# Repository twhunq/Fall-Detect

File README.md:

# Hệ thống IoT Phát hiện & Cảnh báo Té ngã (`Fall_detect`)

Hệ thống giám sát và cảnh báo té ngã đa tầng cho người cao tuổi, kết hợp hai nhánh phần cứng AI tại biên (**Edge AI**) và nền tảng **Cloud Realtime**:

1. **Thiết bị đeo TinyML (`firmware/wearable/`)**: Vi điều khiển **ESP32-S3 Super Mini** + cảm biến quán tính 6 trục **MPU6050**, chạy mô hình mạng nơ-ron **MLP (30 → 16 → 8 → 5)** kết hợp xác nhận động học sau va đập, cảnh báo còi/LED tại chỗ, cấu hình qua Web Portal nội bộ, đồng bộ **Firebase Realtime Database** và gửi tin khẩn cấp qua **Telegram / Gmail**.
2. **Thiết bị Camera AI (`firmware/camera-k230/`)**: Camera **CanMV K230** chạy mô hình thị giác **YOLOv5n** + bộ theo dõi đa đối tượng IoU + bỏ phiếu M-trong-N, kết nối UART tốc độ cao (`921600 baud`) sang **ESP32-S3 DevKitC-1 N16R8** để phát cảnh báo **BLE 5.0** (xác thực `HMAC-SHA256`), đẩy ảnh bằng chứng lên Relay và phát luồng video trực tiếp **MJPEG**.
3. **Cloud & Web Dashboard (`cloud/`)**: Trang giám sát thời gian thực và phân quyền người dùng trên **Firebase Hosting & Realtime Database**.
4. **Ứng dụng di động "Báo Ngã IoT" (`mobile/`)**: Flutter đa nền tảng (Android `.apk`, iOS `.ipa` chưa ký cài bằng **Sideloadly**), nghe song song 4 đường cảnh báo (UDP LAN, BLE camera, Firebase SSE, Web Portal nội mạng), hú còi/rung/màn hình báo động đỏ khi đường nhanh nhất tới, khử trùng lặp và hợp nhất "Vòng đeo + Camera AI" trong 30 giây.
5. **Phần cứng PCB (`hardware/pcb/`)**: Thiết kế mạch nguyên lý, PCB 2 lớp `60 × 50 mm` (KiCad 10), mô hình 3D `.step`, BOM và file Gerber sẵn sàng gia công.

---

## Cấu trúc thư mục dự án

```text
Fall_detect/
├── firmware/
│   ├── wearable/                  # Thiết bị đeo ESP32-S3 Super Mini + TinyML
│   │   ├── src/
│   │   │   ├── fall_detection_esp32/  # Firmware chính (C++17, header-only)
│   │   │   └── data_collection/       # Sketch thu thập dữ liệu IMU 50Hz CSV
│   │   ├── ml/                    # Sinh dữ liệu mô phỏng & huấn luyện MLP
│   │   │   ├── data/              # Tập dữ liệu huấn luyện (.npz, .csv)
│   │   │   ├── generate_synthetic_data.py
│   │   │   ├── train_model.py
│   │   │   ├── training_info.json
│   │   │   └── requirements.txt
│   │   ├── scripts/               # Công cụ build, nạp firmware & Serial Monitor
│   │   │   ├── flash.py
│   │   │   ├── serial_monitor.py
│   │   │   ├── flash.bat
│   │   │   └── monitor.bat
│   │   ├── tests/                 # Bộ kiểm thử đơn vị C++17 & Python chạy trên host
│   │   └── README.md
│   │
│   └── camera-k230/               # Thiết bị giám sát Camera K230 + ESP32-S3 Bridge
│       ├── include/               # Các module header BLE, HMAC-SHA256, Relay, Telegram
│       ├── src/
│       │   └── main.cpp           # Chương trình cầu nối ESP32-S3 (PlatformIO)
│       ├── k230/
│       │   └── falldown_detect.py # Chương trình thị giác AI trên CanMV K230
│       ├── scripts/
│       │   └── flash_bridge.bat   # Script build & nạp nhanh ESP32-S3 Bridge
│       ├── platformio.ini
│       └── README.md
│
├── cloud/                         # Firebase Hosting & Realtime Database
│   ├── public/                    # Giao diện Web Dashboard (index.html, config.js)
│   ├── database.rules.json        # Luật phân quyền bảo mật RTDB
│   ├── access.example.json        # Mẫu cấu hình cây phân quyền /access
│   ├── firebase.json
│   └── .firebaserc
│
├── mobile/                        # App Flutter "Báo Ngã IoT" (Android APK + iOS IPA Sideloadly)
│   ├── lib/                       # config, core/ (giao thức, hợp nhất cảnh báo), services/, platform/, state/, ui/
│   ├── test/                      # Unit test giao thức/hợp nhất + widget test
│   ├── scripts/                   # flutter_env.ps1, setup_local_sdk.ps1, clean_cache.ps1 (mọi thứ trên D:\dev-tools)
│   └── tools/                     # generate_qr.py (mã QR ghép camera), make_alarm_sound.py
│
├── .github/workflows/build-mobile.yml  # CI: analyze + test + APK (Ubuntu) & IPA chưa ký (macOS)
│
├── hardware/
│   └── pcb/                       # Thiết kế KiCad 10 Schematic, PCB, Gerber, BOM & 3D STEP
│
├── docs/                          # Tài liệu kiểm thử phần cứng, hướng dẫn app & báo cáo
│   ├── huong-dan-app-mobile.md
│   ├── validation.md
│   └── reports/
│
└── .gitignore
```

---

## Hướng dẫn nhanh (Quickstart)

### 1. Thiết bị đeo TinyML (`firmware/wearable/`)
```powershell
cd firmware/wearable

# Chạy toàn bộ kiểm thử đơn vị C++17 + Python trên máy tính:
python tests/run_tests.py

# Biên dịch kiểm tra cả 2 sketch (Arduino-ESP32 core 3.3.8):
python scripts/flash.py --build-only
python scripts/flash.py --build-only --sketch data_collection

# Biên dịch & nạp vào mạch ESP32-S3 Super Mini:
python scripts/flash.py --port COM7
python scripts/serial_monitor.py --port COM7
```
Xem chi tiết cấu hình `secrets.h`, hiệu chỉnh cảm biến và Web Portal tại [`firmware/wearable/README.md`](firmware/wearable/README.md).

### 2. Thiết bị Camera K230 + Cầu nối ESP32-S3 (`firmware/camera-k230/`)
```powershell
cd firmware/camera-k230

# Biên dịch firmware cầu nối ESP32-S3 bằng PlatformIO:
pio run -e camera_bridge

# Biên dịch & nạp qua cổng UART trên DevKitC-1:
scripts\flash_bridge.bat COM3
```
Chép [`firmware/camera-k230/k230/falldown_detect.py`](firmware/camera-k230/k230/falldown_detect.py) vào thẻ nhớ CanMV K230 theo hướng dẫn tại [`firmware/camera-k230/README.md`](firmware/camera-k230/README.md).

### 3. Triển khai Cloud Dashboard (`cloud/`)
```powershell
cd cloud
npx firebase-tools login
npx firebase-tools deploy
```

### 4. Mạch in PCB (`hardware/pcb/`)
Mở [`hardware/pcb/fall_detector.kicad_pro`](hardware/pcb/fall_detector.kicad_pro) bằng **KiCad 10** hoặc dùng trực tiếp gói sản xuất [`hardware/pcb/production/fall_detector_gerber.zip`](hardware/pcb/production/fall_detector_gerber.zip). Chi tiết sơ đồ chân và linh kiện xem tại [`hardware/pcb/README.md`](hardware/pcb/README.md).

### 5. Ứng dụng di động "Báo Ngã IoT" (`mobile/`)
Mọi SDK và cache nằm trên `D:\dev-tools\` (không ghi vào ổ `C:`):
```powershell
. .\mobile\scripts\flutter_env.ps1      # Lần đầu tự tải Flutter stable về D:\dev-tools\flutter
cd mobile
flutter pub get
flutter analyze
flutter test

# Tự đóng gói APK trên Windows (tùy chọn): cài JDK 17 + Android SDK vào D:\dev-tools
powershell -ExecutionPolicy Bypass -File scripts\setup_local_sdk.ps1
flutter build apk --release --split-per-abi

# Dọn cache/tạm sau khi làm xong (D:\dev-tools\cache, D:\dev-tools\temp, build/, .dart_tool/)
powershell -ExecutionPolicy Bypass -File scripts\clean_cache.ps1
```
- **Android**: tải `app-arm64-v8a-release.apk` (hoặc `app-release.apk`) từ artifact CI `baonga-android`, cài trực tiếp. App không xin quyền SMS/gọi điện; nút SOS mở trình quay số (`tel:`).
- **iOS**: tải `baonga-ios-unsigned.ipa` từ artifact CI `baonga-ios-unsigned`, kéo thả vào **Sideloadly** và ký bằng Apple ID miễn phí (hiệu lực 7 ngày). Ứng dụng không dùng entitlement trả phí (Push, App Groups, Multicast); cảnh báo UDP tới iPhone bằng unicast.
- **Mã QR ghép camera**: `python mobile/tools/generate_qr.py --mac <MAC cầu nối> --out mobile/qr` (MASTER_KEY qua `--master` hoặc biến `BAONGA_MASTER_KEY`; lấy MAC bằng lệnh `WHOAMI` trên Serial của cầu nối).
- Chi tiết cài đặt từng bước (cấp quyền nền Android, Sideloadly + tự gia hạn 7 ngày trên iOS, kiểm tra độ trễ): [`docs/huong-dan-app-mobile.md`](docs/huong-dan-app-mobile.md).

---

## Đường truyền cảnh báo "Thời gian vàng" (5 lớp)

| Lớp | Cơ chế | Vị trí |
|---|---|---|
| 1 | **UDP LAN Emergency Burst**: `BAONGA|1|<seq>|<device_id>|<FALL\|INACTIVE\|RESUMED>|<metric>|<ip>` tới cổng `4210`, 3 gói cách 20 ms (broadcast + unicast tới 4 điện thoại gần nhất đã gọi Web Portal) | `firmware/wearable/.../lan_alert_*.h`, `firmware/camera-k230/include/lan_alert_udp.h` |
| 2 | **BLE không chặn**: NOTIFY đầu tại 0 ms, 2 lần lặp mỗi 400 ms trong `BleAlert::loop()` (bỏ `delay(400)`) | `firmware/camera-k230/include/ble_alert.h` |
| 3 | **Thiết lập kết nối trước** (*connection pre-warming*) khi va đập ≥ 2 g làm phát sinh sự kiện nghi ngã: tắt Modem Sleep ~10 s, dựng sẵn phiên TLS Firebase; sự kiện bị loại bỏ thì không phát gì | `notifier.h` (`boost`), `cloud_sync.h` (`prewarm`) |
| 4 | **Zero-Wait & Fast-Flush**: cập nhật trạng thái ngay, đánh thức tác vụ bằng task notification, `TCP_NODELAY`; đẩy `alarm` lên Firebase trên phiên TLS dựng sẵn (keep-alive) rồi nhường `TlsGate` cho Telegram → Gmail (luôn tối đa 1 phiên TLS) | `fall_detection_esp32.ino`, `cloud_sync.h` |
| 5 | **Đua đa kênh & hợp nhất**: app nghe UDP + BLE + Firebase SSE + Web Portal; gói tới trước kích hoạt báo động, bản lặp bị khử; vòng đeo + camera trong 30 s → "ĐA NGUỒN XÁC NHẬN" | `mobile/lib/core/fusion/` |

---

## Đóng góp và giấy phép

- Dự án mã nguồn mở, hoan nghênh mọi người cùng phát triển: mở **issue** để báo lỗi hoặc đề xuất, gửi **pull request** cho bản sửa. Hướng đang cần: tối ưu mô hình và năng lượng, đưa lõi phát hiện lên kính AI, đồng hồ, quần áo thông minh; góp dữ liệu và kịch bản thử.
- Không đưa thông tin bí mật vào commit: dùng các tệp mẫu `secrets.example.h`, `device_secrets.example.h`, `k230_wifi.example.json` (bản thật đã gitignore).
- Giấy phép: [MIT](LICENSE) © 2026 Marine (Tuấn Hưng).

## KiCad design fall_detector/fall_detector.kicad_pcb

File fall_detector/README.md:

# Mạch phát hiện té ngã – ESP32-S3 SuperMini + MPU6050

Project KiCad 10: sơ đồ nguyên lý, PCB 2 lớp 60 × 50 mm, file Gerber sẵn để đặt mạch.

## Cấu trúc thư mục

| Đường dẫn | Nội dung |
|---|---|
| `fall_detector.kicad_pro/.kicad_sch/.kicad_pcb` | Project KiCad (mở bằng KiCad 10) |
| `lib/` | Symbol + footprint tự tạo (SuperMini, GY-521, TTP223, công tắc SS12D00) |
| `docs/fall_detector_schematic.pdf` | Sơ đồ nguyên lý dạng PDF |
| `docs/pcb_top_3d.png`, `docs/pcb_iso_3d.png` | Ảnh render 3D |
| `production/fall_detector_gerber.zip` | **Gerber + file khoan – upload thẳng lên JLCPCB/PCBWay** |
| `production/bom.csv` | Danh sách linh kiện |
| `scripts/` | Script dựng lại PCB (đặt linh kiện + đi dây cố định; tùy chọn autoroute Freerouting) |

## Nguyên lý

- **Nguồn**: pin Li-Po 3.7 V → module sạc **TP4056 (loại có mạch bảo vệ)** → `J1` → công tắc `SW1` → diode Schottky `D2` 1N5817 → chân **5V** của SuperMini.
  Theo sơ đồ của Nologo, chân 5V nối thẳng VBUS của cổng USB-C và đầu vào LDO ME6217C33 (800 mA) → 3V3.
  `D2` ngăn dòng 5V từ cổng USB-C của SuperMini chảy ngược vào pin khi đang nạp code, và chặn luôn trường hợp cắm ngược cực pin.
- **Đo pin**: cầu phân áp `R4`/`R5` 100k + `C4` 100nF → GPIO1. `Vpin = Vadc × 2`.
- **MPU6050 (GY-521)**: I2C, `AD0` nối GND → địa chỉ `0x68`. GY-521 có sẵn điện trở kéo lên nên không cần thêm. Chân `INT` dùng để đánh thức ESP32 khỏi deep sleep khi có chuyển động.
- **Còi**: `Q1` S8050 đóng cắt phía GND, `R1` 1k hạn dòng base, `R2` 10k giữ còi tắt lúc ESP32 khởi động, `D1` 1N4148 dập xung ngược. Còi 3 V cấp từ 3V3.
- **LED**: `R3` 330 Ω → khoảng 4 mA với LED đỏ.
- **Nút chạm TTP223**: ngõ ra mức cao khi chạm → GPIO4 (dùng để hủy báo động / gọi SOS).
- Tụ `C1` 100 µF giữ ổn định 3V3 khi còi kêu; `C2`, `C3` 100 nF lọc nguồn sát từng module.

## Sơ đồ chân cho firmware

| Chức năng | GPIO | Ghi chú |
|---|---|---|
| I2C SDA (MPU6050) | 8 | `Wire.begin(8, 9)` |
| I2C SCL (MPU6050) | 9 | |
| MPU6050 INT | 7 | Chân RTC → dùng được cho wake-up từ deep sleep |
| TTP223 OUT | 4 | HIGH khi chạm |
| Còi | 5 | HIGH = kêu (còi thụ động thì dùng `ledcWriteTone`) |
| LED | 6 | HIGH = sáng |
| Đo điện áp pin | 1 | ADC1_CH0, nhân 2 |

Đã tránh các chân strapping (GPIO0, 3, 45, 46). LED RGB trên SuperMini vẫn dùng được ở GPIO48.

## Danh sách linh kiện (đều dễ mua ở VN: Hshop, ICDayRoi, Shopee, chợ Nhật Tảo, chợ Trời…)

| Ký hiệu | Linh kiện | SL | Ghi chú khi mua |
|---|---|---|---|
| U1 | ESP32-S3 SuperMini | 1 | Kèm 2 hàng rào **cái** 1×9 2.54 mm để cắm/tháo |
| U2 | Module GY-521 MPU6050 | 1 | Hàng rào cái 1×8 |
| U3 | Module cảm biến chạm TTP223 | 1 | Hàng rào cái 1×3 |
| BZ1 | Còi chip 3 V (12 × 9.5 mm, chân cách 7.6 mm) | 1 | Loại "còi chủ động 3V" |
| Q1 | Transistor S8050 (TO-92) | 1 | Thay được bằng 2N2222A / PN2222A / 2N3904 (cùng thứ tự E-B-C). **Không** dùng C1815 (thứ tự E-C-B) |
| D1 | Diode 1N4148 | 1 | |
| D2 | Diode Schottky 1N5817 | 1 | 1N5819 cũng dùng được nhưng sụt áp cao hơn (chênh tới ~0.1 V khi dòng lớn) |
| D3 | LED 5 mm đỏ | 1 | |
| R1 | Điện trở 1 kΩ 1/4 W | 1 | |
| R2 | Điện trở 10 kΩ 1/4 W | 1 | |
| R3 | Điện trở 330 Ω 1/4 W | 1 | |
| R4, R5 | Điện trở 100 kΩ 1/4 W | 2 | |
| C1 | Tụ hóa 100 µF 16 V (Ø5–6.3 mm) | 1 | |
| C2–C4 | Tụ gốm 104 (100 nF) | 3 | Chân 5 mm (bẻ chân nếu là loại 2.54 mm) |
| J1 | Đầu JST PH 2.0 mm 2 chân (đứng) | 1 | Nối vào OUT+/OUT− của TP4056 |
| SW1 | Công tắc gạt SS12D00 (3 chân) | 1 | Lỗ oval 1.4 × 1.0 mm nhận cả loại chân 2.0 mm và 2.54 mm |
| – | Module sạc TP4056 Type-C có bảo vệ + pin Li-Po 3.7 V | 1 | Nằm ngoài PCB |
| H1–H4 | Ốc M3 + trụ đồng | 4 | |

## Thông số PCB

- 2 lớp, 60 × 50 mm, bo góc R2, 4 lỗ M3.
- Toàn bộ linh kiện xuyên lỗ (hàn tay dễ), **không có via**.
- Đường tín hiệu 0.3 mm, đường nguồn 0.5 mm, khoảng cách tối thiểu 0.25 mm, phủ đồng GND cả hai mặt.
- Không phủ đồng / không đi dây dưới ăng-ten gốm của SuperMini (đầu xa cổng USB-C); lớp trên không phủ đồng dưới nửa dưới module.
- Chữ in lụa cao 1.0 mm, nét 0.15 mm (mức tối thiểu của JLCPCB/PCBWay).
- DRC (KiCad 10): **0 lỗi, 0 chưa nối, 0 lệch so với sơ đồ**. ERC: 0 lỗi.
- Đặt mạch: upload `production/fall_detector_gerber.zip` lên JLCPCB/PCBWay, để thông số mặc định (FR-4 1.6 mm, HASL).

## ⚠ Kiểm tra trước khi đặt mạch / hàn

1. **Thứ tự chân SuperMini**: footprint (nhìn từ trên, cổng USB-C hướng lên):
   cột trái `TX, RX, 1, 2, 3, 4, 5, 6, 7`; cột phải `5V, GND, 3V3, 13, 12, 11, 10, 9, 8`; hai hàng cách nhau 15.24 mm.
   Đã đối chiếu với ảnh pinout và bản vẽ kích thước 23.5 × 18 mm của Nologo ESP32-S3 SuperMini. Tên chân được in lụa lên PCB – vẫn nên so với board thật.
2. **Chiều cắm GY-521**: hàn hàng rào đực vào GY-521 như bình thường (nhựa ở mặt dưới, linh kiện hướng lên).
   Khi cắm: `VCC` vào lỗ vuông trên cùng, thân module chìa sang **phải** (xa ESP32). Nếu thân module chìa về phía ESP32 là đang cắm ngược.
3. **Thứ tự chân TTP223**: footprint dùng `GND, I/O, VCC` (xem nhãn in lụa). Chân giữa luôn là I/O nhưng hai đầu VCC/GND đảo nhau tùy hãng –
   cắm theo **tên chân**, không theo hình khung; cắm ngược là đảo cực nguồn module.
4. **Cực tính pin**: chân `+` của J1 ở bên trái (có in lụa `+ −`). Kiểm tra dây pin/TP4056 trước khi cắm.
5. Khi cắm USB-C vào SuperMini để nạp code, pin **không** được sạc qua cổng này – hãy sạc qua cổng USB của module TP4056.
   Bản SuperMini có mạch sạc riêng (pad `B+`/`B−` + jumper BOOST ở mặt dưới, IC TP4054) – mạch này **không dùng** pad đó.
   Khi chạy bằng pin, đèn `BAT` xanh trên SuperMini có thể chớp mờ vì IC sạc thấy điện áp ở VBUS mà không có pin: bình thường, không hại gì.

## Thay đổi so với v1.0

- **Sửa footprint GY-521 bị lật gương**: v1.0 đặt `VCC` ở dưới cùng, nên khi cắm module đúng chân thì thân module (16 mm) đè lên ESP32 SuperMini.
  v1.1 đặt `VCC` ở trên cùng, thân module chìa sang phải – khớp module thật (đối chiếu 3 footprint GY-521 độc lập).
- Chân GPIO **giữ nguyên** (firmware không cần sửa); đi dây lại quanh GY-521, `C2` dời lên sát chân VCC của GY-521.
- `C1` (tụ hóa vỏ nhôm) dời xa ăng-ten; bỏ phủ đồng / đường mạch dưới ăng-ten SuperMini.
- `D2` đổi 1N5819 → 1N5817 (sụt áp thấp hơn, cùng footprint DO-41).
- Chữ in lụa 0.8 mm / nét 0.12 mm → 1.0 mm / 0.15 mm (dễ đọc hơn khi gia công).
- Lỗ công tắc SS12D00 nới rộng (lỗ giữa 0.8 → 1.0 mm, rãnh oval 0.8 → 1.0 mm).

## Dựng lại PCB từ sơ đồ (tùy chọn)

Mặc định chỉ cần mở file `.kicad_pcb` bằng KiCad. Nếu muốn dựng lại toàn bộ bằng script (không cần Java):

```sh
KB="$LOCALAPPDATA/Programs/KiCad/10.0/bin"
"$KB/kicad-cli" sch export netlist --format kicadsexpr -o net.net fall_detector.kicad_sch
"$KB/python" scripts/build_pcb.py net.net            # đặt linh kiện, viền board, netclass
"$KB/python" scripts/route_manual.py                 # đi dây cố định + vùng cấm ăng-ten + phủ GND
```

Có thể thay bước cuối bằng autoroute Freerouting (cần Java 25 và `freerouting.jar` v2.4+):
`"$KB/python" scripts/route_pcb.py <java.exe> <freerouting.jar> <thư_mục_tạm>`.

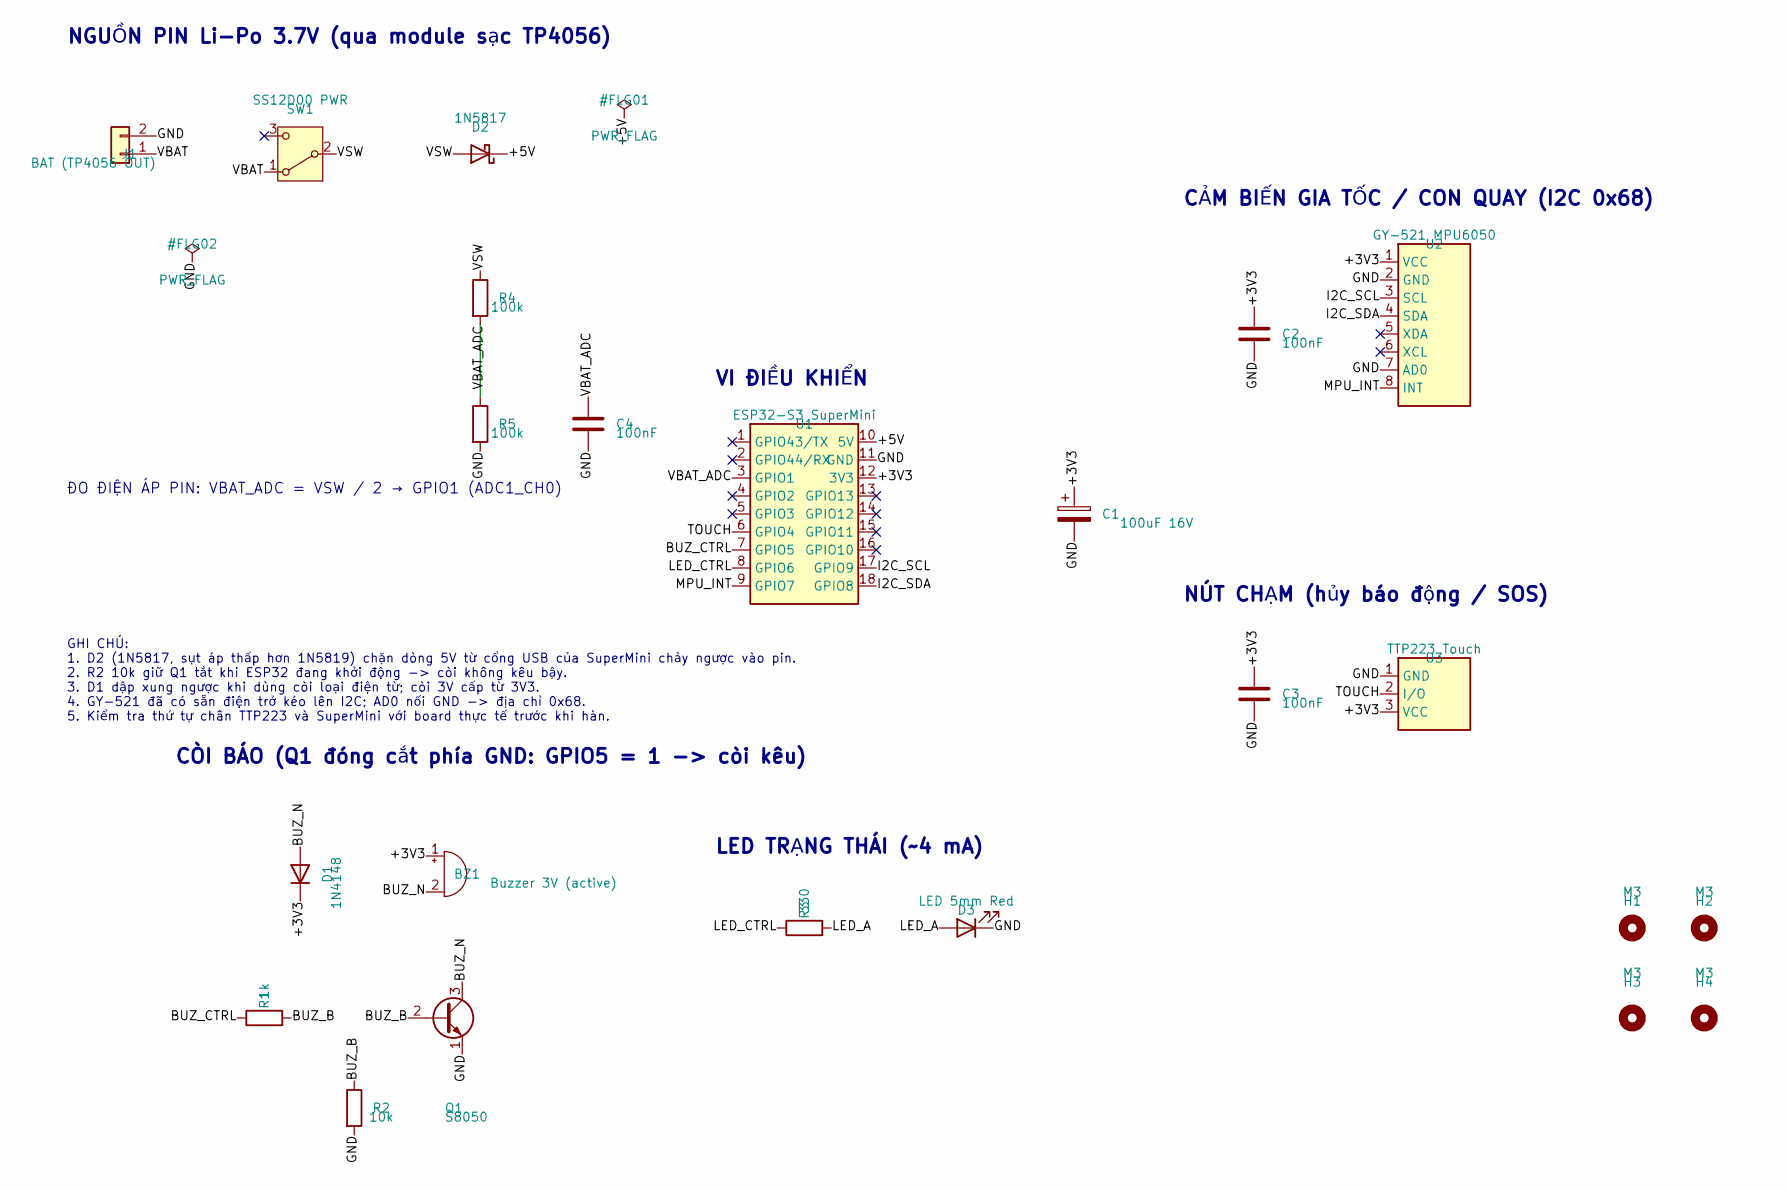
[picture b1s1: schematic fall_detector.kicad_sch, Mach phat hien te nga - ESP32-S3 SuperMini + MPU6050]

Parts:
BZ1: Buzzer 3V (active); Buzzer_12x9.5RM7.6
C1: 100uF 16V; CP_Radial_D6.3mm_P2.50mm
C2, C3, C4: 100nF; C_Disc_D5.0mm_W2.5mm_P5.00mm
D1: 1N4148; D_DO-35_SOD27_P7.62mm_Horizontal
D2: 1N5817; D_DO-41_SOD81_P10.16mm_Horizontal
D3: LED 5mm Red; LED_D5.0mm
H1, H2, H3, H4: M3; MountingHole_3.2mm_M3
J1: BAT (TP4056 OUT); JST_PH_B2B-PH-K_1x02_P2.00mm_Vertical
Q1: S8050; TO-92_Inline_Wide
R1: 1k; R_Axial_DIN0207_L6.3mm_D2.5mm_P7.62mm_Horizontal
R2: 10k; R_Axial_DIN0207_L6.3mm_D2.5mm_P7.62mm_Horizontal
R3: 330; R_Axial_DIN0207_L6.3mm_D2.5mm_P7.62mm_Horizontal
R4, R5: 100k; R_Axial_DIN0207_L6.3mm_D2.5mm_P7.62mm_Horizontal
SW1: SS12D00 PWR; SW_Slide_SS12D00
U1: ESP32-S3 SuperMini; ESP32-S3_SuperMini_Socket
U2: GY-521 MPU6050; GY-521_MPU6050_Module
U3: TTP223 Touch; TTP223_Module

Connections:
/+3V3: BZ1.1 (+), C1.1, C2.1, C3.1, D1.1 (K), U1.12 (3V3), U2.1 (VCC), U3.3 (VCC)
/+5V: D2.1 (K), U1.10 (5V)
/BUZ_B: Q1.2 (B), R1.2, R2.1
/BUZ_CTRL: R1.1, U1.7 (GPIO5)
/BUZ_N: BZ1.2 (-), D1.2 (A), Q1.3 (C)
/GND: C1.2, C2.2, C3.2, C4.2, D3.1 (K), J1.2, Q1.1 (E), R2.2, R5.2, U1.11 (GND), U2.2 (GND), U2.7 (AD0), U3.1 (GND)
/I2C_SCL: U1.17 (GPIO9), U2.3 (SCL)
/I2C_SDA: U1.18 (GPIO8), U2.4 (SDA)
/LED_A: D3.2 (A), R3.2
/LED_CTRL: R3.1, U1.8 (GPIO6)
/MPU_INT: U1.9 (GPIO7), U2.8 (INT)
/TOUCH: U1.6 (GPIO4), U3.2 (I/O)
/VBAT: J1.1, SW1.1 (A)
/VBAT_ADC: C4.1, R4.2, R5.1, U1.3 (GPIO1)
/VSW: D2.2 (A), R4.1, SW1.2 (B)

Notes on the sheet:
NGUỒN PIN Li-Po 3.7V (qua module sạc TP4056)
ĐO ĐIỆN ÁP PIN: VBAT_ADC = VSW / 2 → GPIO1 (ADC1_CH0)
VI ĐIỀU KHIỂN
CẢM BIẾN GIA TỐC / CON QUAY (I2C 0x68)
NÚT CHẠM (hủy báo động / SOS)
CÒI BÁO (Q1 đóng cắt phía GND: GPIO5 = 1 -> còi kêu)
LED TRẠNG THÁI (~4 mA)
GHI CHÚ: 1. D2 (1N5817, sụt áp thấp hơn 1N5819) chặn dòng 5V từ cổng USB của SuperMini chảy ngược vào pin. 2. R2 10k giữ Q1 tắt khi ESP32 đang khởi động -> còi không kêu bậy. 3. D1 dập xung ngược khi dùng còi loại điện từ; còi 3V cấp từ 3V3. 4. GY-521 đã có sẵn điện trở kéo lên I2C; AD0 nối GND -> 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

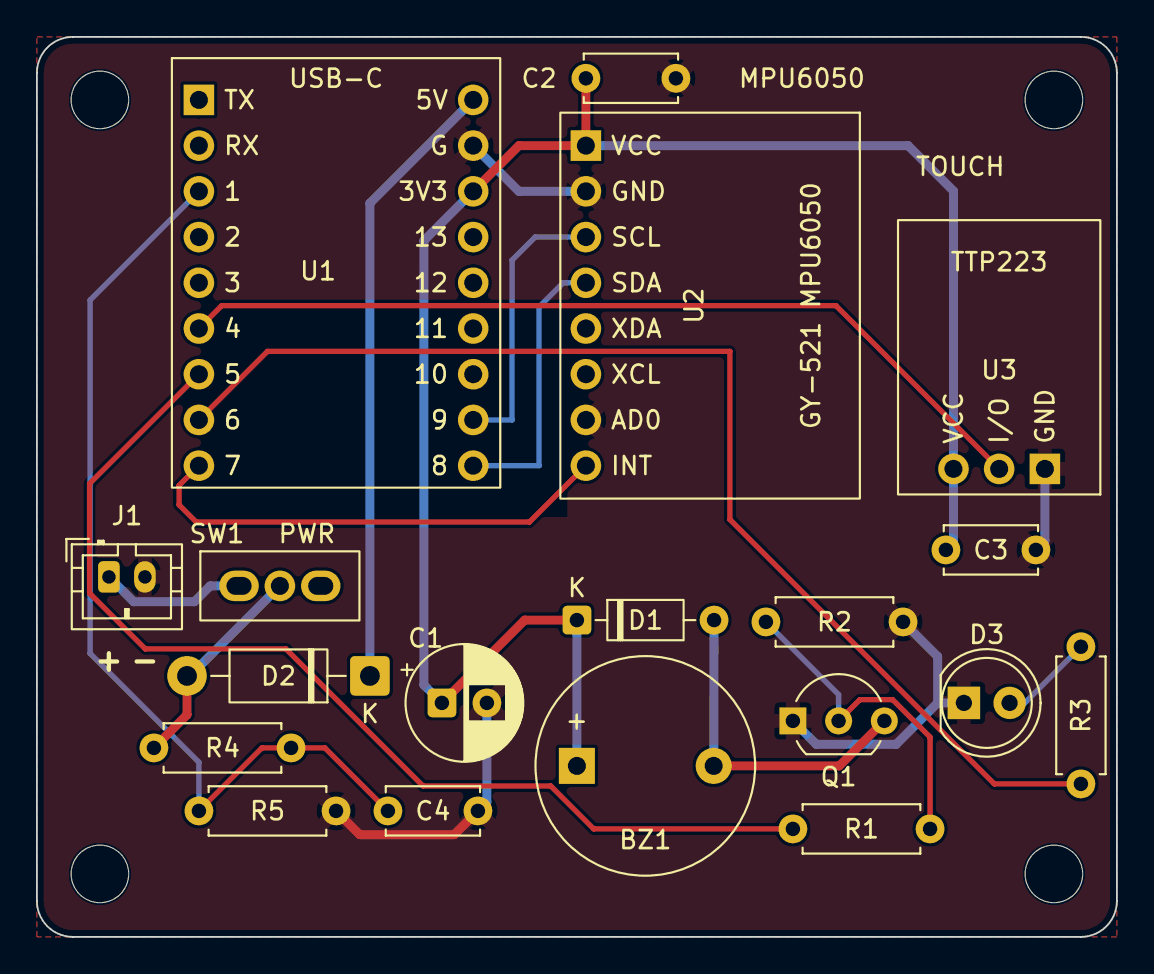
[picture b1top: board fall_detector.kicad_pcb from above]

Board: 2 copper layers, 60.0 x 50.0 mm, 23 parts (0 on the bottom side), 15 nets.

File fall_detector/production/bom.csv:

"Ref","Value","Footprint","Qty"
"BZ1","Buzzer 3V (active)","Buzzer_Beeper:Buzzer_12x9.5RM7.6","1"
"C1","100uF 16V","Capacitor_THT:CP_Radial_D6.3mm_P2.50mm","1"
"C2-C4","100nF","Capacitor_THT:C_Disc_D5.0mm_W2.5mm_P5.00mm","3"
"D1","1N4148","Diode_THT:D_DO-35_SOD27_P7.62mm_Horizontal","1"
"D2","1N5817","Diode_THT:D_DO-41_SOD81_P10.16mm_Horizontal","1"
"D3","LED 5mm Red","LED_THT:LED_D5.0mm","1"
"J1","BAT (TP4056 OUT)","Connector_JST:JST_PH_B2B-PH-K_1x02_P2.00mm_Vertical","1"
"Q1","S8050","Package_TO_SOT_THT:TO-92_Inline_Wide","1"
"R1","1k","Resistor_THT:R_Axial_DIN0207_L6.3mm_D2.5mm_P7.62mm_Horizontal","1"
"R2","10k","Resistor_THT:R_Axial_DIN0207_L6.3mm_D2.5mm_P7.62mm_Horizontal","1"
"R3","330","Resistor_THT:R_Axial_DIN0207_L6.3mm_D2.5mm_P7.62mm_Horizontal","1"
"R4,R5","100k","Resistor_THT:R_Axial_DIN0207_L6.3mm_D2.5mm_P7.62mm_Horizontal","2"
"SW1","SS12D00 PWR","fall_detector:SW_Slide_SS12D00","1"
"U1","ESP32-S3 SuperMini","fall_detector:ESP32-S3_SuperMini_Socket","1"
"U2","GY-521 MPU6050","fall_detector:GY-521_MPU6050_Module","1"
"U3","TTP223 Touch","fall_detector:TTP223_Module","1"

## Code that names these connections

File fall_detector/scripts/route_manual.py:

"""Route the fall-detector board with fixed tracks, then add the GND pours.

    python.exe scripts/route_manual.py

Run after build_pcb.py; needs no Java/Freerouting. Coordinates are board mm
relative to the top-left corner (same as build_pcb.py). Widths follow the net
classes that build_pcb.py writes: Power 0.5 mm, Default 0.3 mm.
"""
import os

import pcbnew

PRJ = os.path.dirname(os.path.dirname(os.path.abspath(__file__)))
BOARD = os.path.join(PRJ, "fall_detector.kicad_pcb")
BOARD_W, BOARD_H, ORIGIN = 60.0, 50.0, (100.0, 100.0)
POWER_NETS = {"/GND", "/+3V3", "/+5V", "/VBAT", "/VSW", "/BUZ_N"}

# The SuperMini's chip antenna is at the end away from USB-C, ~11 mm above this
# board (x 10.7-17.7, y 23.1-25.4). Keep pour, tracks and vias out from under it,
# and keep the top-layer pour off the rest of the module's lower half.
ANTENNA_KEEPOUT = (10.0, 21.8, 18.0, 26.6)  # x1, y1, x2, y2
TOP_POUR_KEEPOUT = (10.0, 17.7, 29.6, 26.8)

F, B = "F.Cu", "B.Cu"

# net: [(layer, (x1, y1), (x2, y2)), ...]
TRACKS = {
    "/VBAT": [  # J1.1 -> SW1.1
        (B, (4.0, 30.0), (5.378, 31.378)),
        (B, (5.378, 31.378), (8.75, 31.378)),
        (B, (8.75, 31.378), (9.628, 30.5)),
        (B, (9.628, 30.5), (11.23, 30.5)),
    ],
    "/VSW": [  # SW1.2 -> D2 anode -> R4.1
        (B, (13.5, 30.5), (8.5, 35.5)),
        (B, (8.5, 35.5), (8.34, 35.5)),
        (F, (8.34, 35.5), (8.34, 37.66)),
        (F, (8.34, 37.66), (6.5, 39.5)),
    ],
    "/+5V": [  # D2 cathode -> SuperMini 5V (= its USB VBUS / LDO input)
        (B, (24.24, 3.5), (18.5, 9.24)),
        (B, (18.5, 9.24), (18.5, 35.5)),
    ],
    "/+3V3": [
        (F, (24.24, 8.58), (26.78, 6.04)),  # U1 3V3 -> GY-521 VCC
        (F, (26.78, 6.04), (30.5, 6.04)),
        (F, (30.5, 6.04), (30.5, 2.3)),  # -> C2
        (B, (30.5, 6.04), (48.4, 6.04)),  # -> TTP223 VCC, C3
        (B, (48.4, 6.04), (50.92, 8.56)),
        (B, (50.92, 8.56), (50.92, 24.0)),
        (B, (50.92, 24.0), (50.92, 28.08)),
        (B, (50.92, 28.08), (50.5, 28.5)),
        (B, (24.24, 8.58), (21.5, 11.32)),  # U1 3V3 -> C1 -> D1 -> buzzer
        (B, (21.5, 11.32), (21.5, 36.0)),
        (B, (21.5, 36.0), (22.5, 37.0)),
        (F, (22.5, 37.0), (27.1, 32.4)),
        (F, (27.1, 32.4), (30.0, 32.4)),
        (B, (30.0, 32.4), (30.0, 40.5)),
    ],
    "/GND": [  # the pours carry most of GND; these tie the pad clusters together
        (B, (24.24, 6.04), (26.78, 8.58)),  # U1 GND -> GY-521 GND
        (B, (26.78, 8.58), (30.5, 8.58)),
        (B, (56.0, 24.0), (56.0, 28.0)),  # TTP223 GND -> C3
        (B, (56.0, 28.0), (55.5, 28.5)),
        (B, (42.0, 38.0), (43.3, 39.3)),  # Q1 E -> D3 K -> R2
        (B, (43.3, 39.3), (47.74, 39.3)),
        (B, (47.74, 39.3), (50.04, 37.0)),
        (B, (50.04, 37.0), (51.5, 37.0)),
        (B, (50.04, 37.0), (50.04, 34.42)),
        (B, (50.04, 34.42), (48.12, 32.5)),
        (B, (24.5, 43.0), (25.0, 42.5)),  # C4 -> C1
        (B, (25.0, 42.5), (25.0, 37.0)),
        (F, (16.62, 43.0), (17.94, 44.32)),  # R5 -> C4
        (F, (17.94, 44.32), (23.18, 44.32)),
        (F, (23.18, 44.32), (24.5, 43.0)),
    ],
    "/VBAT_ADC": [  # GPIO1 -> R4/R5 divider and C4
        (B, (9.0, 8.58), (2.956, 14.624)),
        (B, (2.956, 14.624), (2.956, 34.256)),
        (B, (2.956, 34.256), (9.0, 40.3)),
        (B, (9.0, 40.3), (9.0, 43.0)),
        (F, (9.0, 43.0), (12.5, 39.5)),
        (F, (12.5, 39.5), (14.12, 39.5)),
        (F, (14.12, 39.5), (16.0, 39.5)),
        (F, (16.0, 39.5), (19.5, 43.0)),
    ],
    "/I2C_SCL": [  # GPIO9 -> SCL, bottom-layer lane between the U1 and U2 headers
        (B, (24.24, 21.28), (26.4, 21.28)),
        (B, (26.4, 21.28), (26.4, 12.4)),
        (B, (26.4, 12.4), (27.68, 11.12)),
        (B, (27.68, 11.12), (30.5, 11.12)),
    ],
    "/I2C_SDA": [  # GPIO8 -> SDA, second lane
        (B, (24.24, 23.82), (27.9, 23.82)),
        (B, (27.9, 23.82), (27.9, 15.0)),
        (B, (27.9, 15.0), (29.24, 13.66)),
        (B, (29.24, 13.66), (30.5, 13.66)),
    ],
    "/MPU_INT": [  # GPIO7 -> INT, below the antenna keep-out
        (F, (9.0, 23.82), (7.9, 24.92)),
        (F, (7.9, 24.92), (7.9, 26.0)),
        (F, (7.9, 26.0), (8.85, 26.95)),
        (F, (8.85, 26.95), (27.37, 26.95)),
        (F, (27.37, 26.95), (30.5, 23.82)),
    ],
    "/TOUCH": [  # GPIO4 -> TTP223 I/O, between unused header pins (U1 14/15, U2 SDA/XDA)
        (F, (9.0, 16.2), (10.27, 14.93)),
        (F, (10.27, 14.93), (44.39, 14.93)),
        (F, (44.39, 14.93), (53.46, 24.0)),
    ],
    "/LED_CTRL": [  # GPIO6 -> R3, above the antenna, between unused header pins (U1 15/16, U2 XDA/XCL)
        (F, (9.0, 21.28), (12.81, 17.47)),
        (F, (12.81, 17.47), (38.5, 17.47)),
        (F, (38.5, 17.47), (38.5, 26.81)),
        (F, (38.5, 26.81), (53.19, 41.5)),
        (F, (53.19, 41.5), (58.0, 41.5)),
    ],
    "/LED_A": [
        (B, (54.04, 37.0), (54.88, 37.0)),
        (B, (54.88, 37.0), (58.0, 33.88)),
    ],
    "/BUZ_CTRL": [  # GPIO5 -> R1
        (F, (9.0, 18.74), (2.928, 24.812)),
        (F, (2.928, 24.812), (2.928, 30.908)),
        (F, (2.928, 30.908), (6.019, 33.998)),
        (F, (6.019, 33.998), (13.833, 33.998)),
        (F, (13.833, 33.998), (21.45, 41.616)),
        (F, (21.45, 41.616), (28.548, 41.616)),
        (F, (28.548, 41.616), (30.932, 44.0)),
        (F, (30.932, 44.0), (42.0, 44.0)),
    ],
    "/BUZ_B": [
        (F, (44.54, 38.0), (45.718, 36.822)),
        (F, (45.718, 36.822), (47.543, 36.822)),
        (F, (47.543, 36.822), (49.62, 38.9)),
        (F, (49.62, 38.9), (49.62, 44.0)),
        (B, (44.54, 38.0), (44.54, 36.54)),
        (B, (44.54, 36.54), (40.5, 32.5)),
    ],
    "/BUZ_N": [
        (F, (47.08, 38.0), (44.58, 40.5)),
        (F, (44.58, 40.5), (37.6, 40.5)),
        (B, (37.6, 40.5), (37.62, 32.4)),
    ],
}


def pt(x, y):
    return pcbnew.VECTOR2I(pcbnew.FromMM(ORIGIN[0] + x), pcbnew.FromMM(ORIGIN[1] + y))


def rect_outline(zone, x1, y1, x2, y2):
    ol = zone.Outline()
    ol.NewOutline()
    for x, y in [(x1, y1), (x2, y1), (x2, y2), (x1, y2)]:
        ol.Append(pcbnew.FromMM(ORIGIN[0] + x), pcbnew.FromMM(ORIGIN[1] + y))


def add_gnd_zone(board, layer, net):
    z = pcbnew.ZONE(board)
    z.SetLayer(layer)
    z.SetNetCode(net.GetNetCode())
    z.SetLocalClearance(pcbnew.FromMM(0.3))
    z.SetMinThickness(pcbnew.FromMM(0.25))
    z.SetPadConnection(pcbnew.ZONE_CONNECTION_THERMAL)
    z.SetThermalReliefGap(pcbnew.FromMM(0.4))
    z.SetThermalReliefSpokeWidth(pcbnew.FromMM(0.5))
    rect_outline(z, 0, 0, BOARD_W, BOARD_H)
    board.Add(z)


def add_rule_area(board, name, layers, rect, tracks):
    z = pcbnew.ZONE(board)
    z.SetIsRuleArea(True)
    z.SetZoneName(name)
    z.SetLayerSet(layers)
    z.SetDoNotAllowZoneFills(True)
    z.SetDoNotAllowTracks(tracks)
    z.SetDoNotAllowVias(True)
    z.SetDoNotAllowPads(False)
    z.SetDoNotAllowFootprints(False)
    rect_outline(z, *rect)
    board.Add(z)


def add_antenna_keepout(board):
    add_rule_area(board, "ANTENNA_KEEPOUT", pcbnew.LSET.AllCuMask(2), ANTENNA_KEEPOUT, True)
    top = pcbnew.LSET()
    top.AddLayer(pcbnew.F_Cu)
    add_rule_area(board, "TOP_POUR_KEEPOUT", top, TOP_POUR_KEEPOUT, False)


def add_zones(board):
    gnd = board.FindNet("/GND")
    add_gnd_zone(board, pcbnew.B_Cu, gnd)
    add_gnd_zone(board, pcbnew.F_Cu, gnd)
    pcbnew.ZONE_FILLER(board).Fill(board.Zones())


def main():
    board = pcbnew.LoadBoard(BOARD)
    for t in list(board.GetTracks()):
        board.Delete(t)
    for i in reversed(range(board.GetAreaCount())):
        board.Delete(board.GetArea(i))
    add_antenna_keepout(board)

    layers = {F: pcbnew.F_Cu, B: pcbnew.B_Cu}
    count = 0
    for name, segs in TRACKS.items():
        net = board.FindNet(name)
        if net is None:
            raise SystemExit(f"net not on board: {name}")
        width = pcbnew.FromMM(0.5 if name in POWER_NETS else 0.3)
        for layer, a, b in segs:
            t = pcbnew.PCB_TRACK(board)
            t.SetLayer(layers[layer])
            t.SetStart(pt(*a))
            t.SetEnd(pt(*b))
            t.SetWidth(width)
            t.SetNet(net)
            board.Add(t)
            count += 1

    add_zones(board)
    board.Save(BOARD)
    print("tracks:", count)


if __name__ == "__main__":
    main()
